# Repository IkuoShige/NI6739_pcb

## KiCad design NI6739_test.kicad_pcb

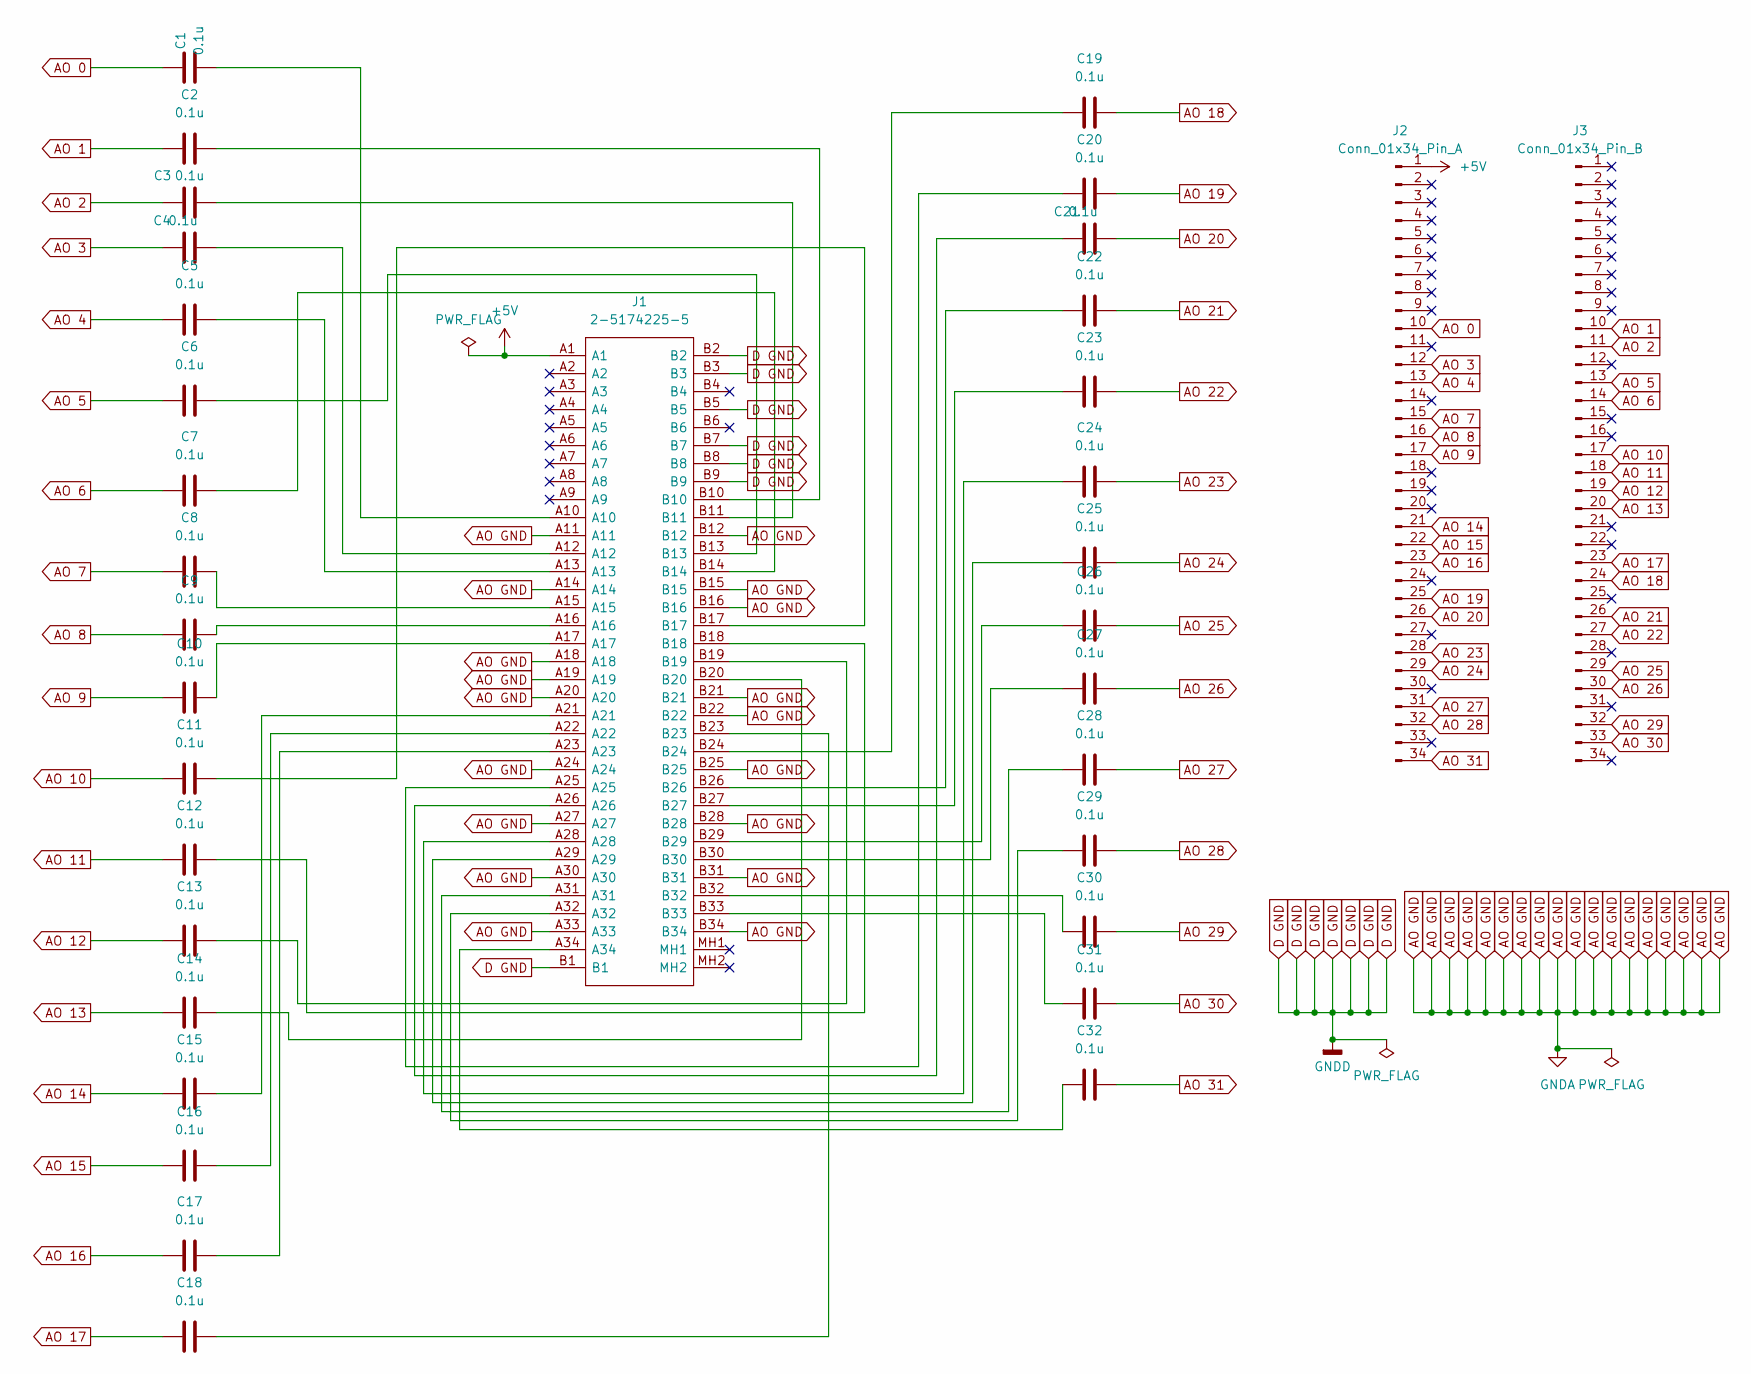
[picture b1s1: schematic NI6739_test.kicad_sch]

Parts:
C1, C2, C3, C4, C5, C6, C7, C8, C9, C10, C11, C12, C13, C14, C15, C16, C17, C18, C19, C20, C21, C22, C23, C24, C25, C26, C27, C28, C29, C30, C31, C32: 0.1u; C_0603_1608Metric
J1: 2-5174225-5; 251742255; Mouser Part Number 571-2-5174225-5
J2: Conn_01x34_Pin_A; PinHeader_1x34_P1.00mm_Vertical_SMD_Pin1Left
J3: Conn_01x34_Pin_B; PinHeader_1x34_P1.00mm_Vertical_SMD_Pin1Left

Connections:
+5V: J1.A1, J2.1
AO 0: C1.1, J2.10
AO 1: C2.1, J3.10
AO 2: C3.1, J3.11
AO 3: C4.1, J2.12
AO 4: C5.1, J2.13
AO 5: C6.1, J3.13
AO 6: C7.1, J3.14
AO 7: C8.1, J2.15
AO 8: C9.1, J2.16
AO 9: C10.1, J2.17
AO 10: C11.1, J3.17
AO 11: C12.1, J3.18
AO 12: C13.1, J3.19
AO 13: C14.1, J3.20
AO 14: C15.1, J2.21
AO 15: C16.1, J2.22
AO 16: C17.1, J2.23
AO 17: C18.1, J3.23
AO 18: C19.2, J3.24
AO 19: C20.2, J2.25
AO 20: C21.2, J2.26
AO 21: C22.2, J3.26
AO 22: C23.2, J3.27
AO 23: C24.2, J2.28
AO 24: C25.2, J2.29
AO 25: C26.2, J3.29
AO 26: C27.2, J3.30
AO 27: C28.2, J2.31
AO 28: C29.2, J2.32
AO 29: C30.2, J3.32
AO 30: C31.2, J3.33
AO 31: C32.2, J2.34
AO GND: J1.A11, J1.A14, J1.A18, J1.A19, J1.A20, J1.A24, J1.A27, J1.A30, J1.A33, J1.B12, J1.B15, J1.B16, J1.B21, J1.B22, J1.B25, J1.B28, J1.B31, J1.B34
D GND: J1.B1, J1.B2, J1.B3, J1.B5, J1.B7, J1.B8, J1.B9
unnamed: C1.2, J1.A10
unnamed: C2.2, J1.B10
unnamed: C3.2, J1.B11
unnamed: C4.2, J1.A12
unnamed: C5.2, J1.A13
unnamed: C6.2, J1.B13
unnamed: C7.2, J1.B14
unnamed: C8.2, J1.A15
unnamed: C9.2, J1.A16
unnamed: C10.2, J1.A17
unnamed: C11.2, J1.B17
unnamed: C12.2, J1.B18
unnamed: C13.2, J1.B19
unnamed: C14.2, J1.B20
unnamed: C15.2, J1.A21
unnamed: C16.2, J1.A22
unnamed: C17.2, J1.A23
unnamed: C18.2, J1.B23
unnamed: C19.1, J1.B24
unnamed: C20.1, J1.A25
unnamed: C21.1, J1.A26
unnamed: C22.1, J1.B26
unnamed: C23.1, J1.B27
unnamed: C24.1, J1.A28
unnamed: C25.1, J1.A29
unnamed: C26.1, J1.B29
unnamed: C27.1, J1.B30
unnamed: C28.1, J1.A31
unnamed: C29.1, J1.A32
unnamed: C30.1, J1.B32
unnamed: C31.1, J1.B33
unnamed: C32.1, J1.A34

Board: 2 copper layers, 35 parts (0 on the bottom side), 67 nets, no tracks yet.

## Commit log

2024-04-19 Add progress 240419
2024-06-10 Add sch for measure each pin of NI6739 connector
2024-06-10 Add pdf-file that exported from sch
2024-06-13 Add footprint
